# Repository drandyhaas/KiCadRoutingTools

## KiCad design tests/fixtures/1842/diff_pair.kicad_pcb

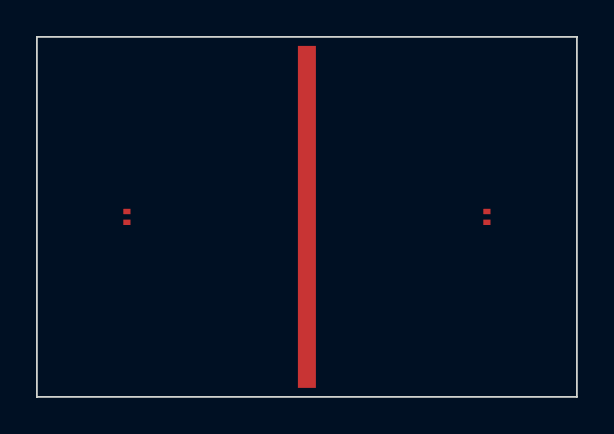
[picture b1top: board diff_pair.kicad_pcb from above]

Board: 8 copper layers, 30.0 x 20.0 mm, 4 parts (0 on the bottom side), 3 nets, no tracks yet.

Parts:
J1: J1
J2: J2
U9: U9
W1: W1

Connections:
/D0_N: J1.2, J2.2
/D0_P: J1.1, J2.1
GND: U9.1, U9.2, U9.3, U9.4, U9.5, U9.6, U9.7, U9.8, U9.9, U9.10, U9.11, U9.12, U9.13, U9.14, U9.15, U9.16, U9.17, U9.18, U9.19, U9.20, U9.21, U9.22, U9.23, U9.24, U9.25, U9.26, U9.27, U9.28, U9.29, U9.30, U9.31, U9.32, U9.33, U9.34, U9.35, U9.36, U9.37, U9.38, U9.39, U9.40, U9.41, U9.42, U9.43, U9.44, U9.45, U9.46, U9.47, U9.48, U9.49, U9.50, U9.51, U9.52, U9.53, U9.54, U9.55, U9.56, U9.57, U9.58, U9.59, U9.60, U9.61, U9.62, U9.63, U9.64, U9.65, U9.66, U9.67, U9.68, U9.69, U9.70, U9.71, U9.72, U9.73, U9.74, U9.75, U9.76, U9.77, U9.78, U9.79, U9.80, U9.81, U9.82, U9.83, U9.84, U9.85, U9.86, U9.87, U9.88, U9.89, U9.90, U9.91, U9.92, U9.93, U9.94, U9.95, U9.96, U9.97, U9.98, U9.99, U9.100, U9.101, U9.102, U9.103, U9.104, U9.105, U9.106, U9.107, U9.108, U9.109, U9.110, U9.111, U9.112, U9.113, U9.114, U9.115, U9.116, U9.117, U9.118, U9.119, U9.120, U9.121, U9.122, U9.123, U9.124, U9.125, U9.126, U9.127, U9.128, U9.129, U9.130, U9.131, U9.132, U9.133, U9.134, U9.135, U9.136, U9.137, U9.138, U9.139, U9.140, U9.141, U9.142, U9.143, U9.144, U9.145, U9.146, U9.147, U9.148, U9.149, U9.150, U9.151, U9.152, U9.153, U9.154, U9.155, U9.156, U9.157, U9.158, U9.159, U9.160, U9.161, U9.162, U9.163, U9.164, U9.165, U9.166, U9.167, U9.168, U9.169, U9.170, U9.171, U9.172, U9.173, U9.174, U9.175, U9.176, U9.177, U9.178, U9.179, U9.180, U9.181, U9.182, U9.183, U9.184, U9.185, U9.186, U9.187, U9.188, U9.189, U9.190, U9.191, U9.192, U9.193, U9.194, U9.195, U9.196, U9.197, U9.198, U9.199, U9.200, U9.201, U9.202, U9.203, U9.204, U9.205, U9.206, U9.207, U9.208, U9.209, U9.210, U9.211, U9.212, U9.213, U9.214, U9.215, U9.216, U9.217, U9.218, U9.219, U9.220, U9.221, U9.222, U9.223, U9.224, U9.225, U9.226, U9.227, U9.228, U9.229, U9.230, U9.231, U9.232, U9.233, U9.234, U9.235, U9.236, U9.237, U9.238, U9.239, U9.240, U9.241, U9.242, U9.243, U9.244, U9.245, U9.246, U9.247, U9.248, U9.249, U9.250, U9.251, U9.252, U9.253, U9.254, U9.255, U9.256, U9.257, U9.258, U9.259, U9.260, U9.261, U9.262, U9.263, U9.264, U9.265, U9.266, U9.267, U9.268, U9.269, U9.270, U9.271, U9.272, U9.273, U9.274, U9.275, U9.276, U9.277, U9.278, U9.279, U9.280, U9.281, U9.282, U9.283, U9.284, U9.285, U9.286, U9.287, U9.288, U9.289, U9.290, U9.291, U9.292, U9.293, U9.294, U9.295, U9.296, U9.297, U9.298, U9.299, U9.300, U9.301, U9.302, U9.303, U9.304, U9.305, U9.306, U9.307, U9.308, U9.309, U9.310, U9.311, U9.312, U9.313, U9.314, U9.315, U9.316, U9.317, U9.318, U9.319, U9.320, U9.321, U9.322, U9.323, U9.324, U9.325, U9.326, U9.327, U9.328, U9.329, U9.330, U9.331, U9.332, U9.333, U9.334, U9.335, U9.336, U9.337, U9.338, U9.339, U9.340, U9.341, U9.342, U9.343, U9.344, U9.345, U9.346, U9.347, U9.348, U9.349, U9.350, U9.351, U9.352, U9.353, U9.354, U9.355, U9.356, U9.357, U9.358, U9.359, U9.360, U9.361, U9.362, U9.363, U9.364, U9.365, U9.366, U9.367, U9.368, U9.369, U9.370, U9.371, U9.372, U9.373, U9.374, U9.375, U9.376, U9.377, U9.378, U9.379, U9.380, U9.381, U9.382, U9.383, U9.384, U9.385, U9.386, U9.387, U9.388, U9.389, U9.390, U9.391, U9.392, U9.393, U9.394, U9.395, U9.396, U9.397, U9.398, U9.399, U9.400, U9.401, U9.402, U9.403, U9.404, U9.405, U9.406, U9.407, U9.408, U9.409, U9.410, U9.411, U9.412, U9.413, U9.414, U9.415, U9.416, U9.417, U9.418, U9.419, U9.420, U9.421, U9.422, U9.423, U9.424, U9.425, U9.426, U9.427, U9.428, U9.429, U9.430, U9.431, U9.432, U9.433, U9.434, U9.435, U9.436, U9.437, U9.438, U9.439, U9.440, U9.441, U9.442, U9.443, U9.444, U9.445, U9.446, U9.447, U9.448, U9.449, U9.450, U9.451, U9.452, U9.453, U9.454, U9.455, U9.456, U9.457, U9.458, U9.459, U9.460, U9.461, U9.462, U9.463, U9.464, U9.465, U9.466, U9.467, U9.468, U9.469, U9.470, U9.471, U9.472, U9.473, U9.474, U9.475, U9.476, U9.477, U9.478, U9.479, U9.480, U9.481, U9.482, U9.483, U9.484, U9.485, U9.486, U9.487, U9.488, U9.489, U9.490, U9.491, U9.492, U9.493, U9.494, U9.495, U9.496, U9.497, U9.498, U9.499, U9.500, U9.501, U9.502, U9.503, U9.504, U9.505, U9.506, U9.507, U9.508, U9.509, U9.510, U9.511, U9.512, U9.513, U9.514, U9.515, U9.516, U9.517, U9.518, U9.519, U9.520, U9.521, U9.522, U9.523, U9.524, U9.525, U9.526, U9.527, U9.528, U9.529, U9.530, U9.531, U9.532, U9.533, U9.534, U9.535, U9.536, U9.537, U9.538, U9.539, U9.540, U9.541, U9.542, U9.543, U9.544, U9.545, U9.546, U9.547, U9.548, U9.549, U9.550, U9.551, U9.552, U9.553, U9.554, U9.555, U9.556, U9.557, U9.558, U9.559, U9.560, U9.561, U9.562, U9.563, U9.564, U9.565, U9.566, U9.567, U9.568, U9.569, U9.570, U9.571, U9.572, U9.573, U9.574, U9.575, U9.576, U9.577, U9.578, U9.579, U9.580, U9.581, U9.582, U9.583, U9.584, U9.585, U9.586, U9.587, U9.588, U9.589, U9.590, U9.591, U9.592, U9.593, U9.594, U9.595, U9.596, U9.597, U9.598, U9.599, U9.600, U9.601, U9.602, U9.603, U9.604, U9.605, U9.606, U9.607, U9.608, U9.609, U9.610, U9.611, U9.612, U9.613, U9.614, U9.615, U9.616, U9.617, U9.618, U9.619, U9.620, U9.621, U9.622, U9.623, U9.624, U9.625, U9.626, U9.627, U9.628, U9.629, U9.630, U9.631, U9.632, U9.633, U9.634, U9.635, U9.636, U9.637, U9.638, U9.639, U9.640, U9.641, U9.642, U9.643, U9.644, U9.645, U9.646, U9.647, U9.648, U9.649, U9.650, U9.651, U9.652, U9.653, U9.654, U9.655, U9.656, U9.657, U9.658, U9.659, U9.660, U9.661, U9.662, U9.663, U9.664, U9.665, U9.666, U9.667, U9.668, U9.669, U9.670, U9.671, U9.672, U9.673, U9.674, U9.675, U9.676, U9.677, U9.678, U9.679, U9.680, U9.681, U9.682, U9.683, U9.684, U9.685, U9.686, U9.687, U9.688, U9.689, U9.690, U9.691, U9.692, U9.693, U9.694, U9.695, U9.696, U9.697, U9.698, U9.699, U9.700, U9.701, U9.702, U9.703, U9.704, U9.705, U9.706, U9.707, U9.708, U9.709, U9.710, U9.711, U9.712, U9.713, U9.714, U9.715, U9.716, U9.717, U9.718, U9.719, U9.720, U9.721, U9.722, U9.723, U9.724, U9.725, U9.726, U9.727, U9.728, U9.729, U9.730, U9.731, U9.732, U9.733, U9.734, U9.735, U9.736, U9.737, U9.738, U9.739, U9.740, U9.741, U9.742, U9.743, U9.744, U9.745, U9.746, U9.747, U9.748, U9.749, U9.750, U9.751, U9.752, U9.753, U9.754, U9.755, U9.756, U9.757, U9.758, U9.759, U9.760, U9.761, U9.762, U9.763, U9.764, U9.765, U9.766, U9.767, U9.768, U9.769, U9.770, U9.771, U9.772, U9.773, U9.774, U9.775, U9.776, U9.777, U9.778, U9.779, U9.780, U9.781, U9.782, U9.783, U9.784, U9.785, U9.786, U9.787, U9.788, U9.789, U9.790, U9.791, U9.792, U9.793, U9.794, U9.795, U9.796, U9.797, U9.798, U9.799, U9.800, U9.801, U9.802, U9.803, U9.804, U9.805, U9.806, U9.807, U9.808, U9.809, U9.810, U9.811, U9.812, U9.813, U9.814, U9.815, U9.816, U9.817, U9.818, U9.819, U9.820, U9.821, U9.822, U9.823, U9.824, U9.825, U9.826, U9.827, U9.828, U9.829, U9.830, U9.831, U9.832, U9.833, U9.834, U9.835, U9.836, U9.837, U9.838, U9.839, U9.840, U9.841, U9.842, U9.843, U9.844, U9.845, U9.846, U9.847, U9.848, U9.849, U9.850, U9.851, U9.852, U9.853, U9.854, U9.855, U9.856, U9.857, U9.858, U9.859, U9.860, U9.861, U9.862, U9.863, U9.864, U9.865, U9.866, U9.867, U9.868, U9.869, U9.870, U9.871, U9.872, U9.873, U9.874, U9.875, U9.876, U9.877, U9.878, U9.879, U9.880, U9.881, U9.882, U9.883, U9.884, U9.885, U9.886, U9.887, U9.888

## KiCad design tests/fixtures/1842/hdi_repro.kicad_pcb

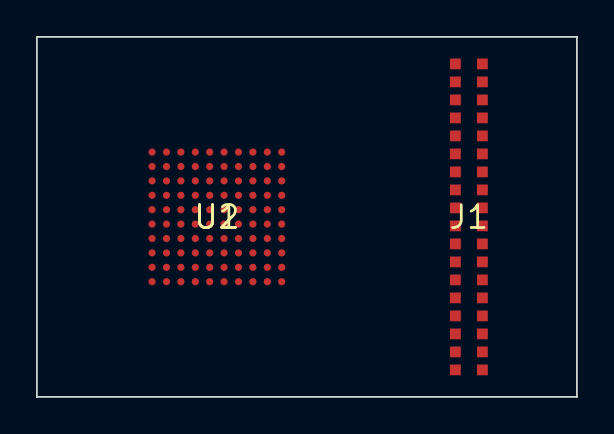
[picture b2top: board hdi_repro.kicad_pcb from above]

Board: 8 copper layers, 30.0 x 20.0 mm, 3 parts (1 on the bottom side), 37 nets, no tracks yet.

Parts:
J1: J1
U1: U1
U2: U2

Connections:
GND: U2.1, U2.2, U2.3, U2.4, U2.5, U2.6, U2.7, U2.8, U2.9, U2.10, U2.11, U2.12, U2.13, U2.14, U2.15, U2.16, U2.17, U2.18, U2.19, U2.20, U2.21, U2.22, U2.23, U2.24, U2.25, U2.26, U2.27, U2.28, U2.29, U2.30, U2.31, U2.32, U2.33, U2.34, U2.35, U2.36, U2.37, U2.38, U2.39, U2.40, U2.41, U2.42, U2.43, U2.44, U2.45, U2.46, U2.47, U2.48, U2.49, U2.50, U2.51, U2.52, U2.53, U2.54, U2.55, U2.56, U2.57, U2.58, U2.59, U2.60, U2.61, U2.62, U2.63, U2.64, U2.65, U2.66, U2.67, U2.68, U2.69, U2.70, U2.71, U2.72, U2.73, U2.74, U2.75, U2.76, U2.77, U2.78, U2.79, U2.80, U2.81
S01: J1.1, U1.C3
S02: J1.2, U1.C4
S03: J1.3, U1.C5
S04: J1.4, U1.C6
S05: J1.5, U1.C7
S06: J1.6, U1.C8
S07: J1.7, U1.D3
S08: J1.8, U1.D4
S09: J1.9, U1.D5
S10: J1.10, U1.D6
S11: J1.11, U1.D7
S12: J1.12, U1.D8
S13: J1.13, U1.E3
S14: J1.14, U1.E4
S15: J1.15, U1.E5
S16: J1.16, U1.E6
S17: J1.17, U1.E7
S18: J1.18, U1.E8
S19: J1.19, U1.F3
S20: J1.20, U1.F4
S21: J1.21, U1.F5
S22: J1.22, U1.F6
S23: J1.23, U1.F7
S24: J1.24, U1.F8
S25: J1.25, U1.G3
S26: J1.26, U1.G4
S27: J1.27, U1.G5
S28: J1.28, U1.G6
S29: J1.29, U1.G7
S30: J1.30, U1.G8
S31: J1.31, U1.H3
S32: J1.32, U1.H4
S33: J1.33, U1.H5
S34: J1.34, U1.H6
S35: J1.35, U1.H7
S36: J1.36, U1.H8
